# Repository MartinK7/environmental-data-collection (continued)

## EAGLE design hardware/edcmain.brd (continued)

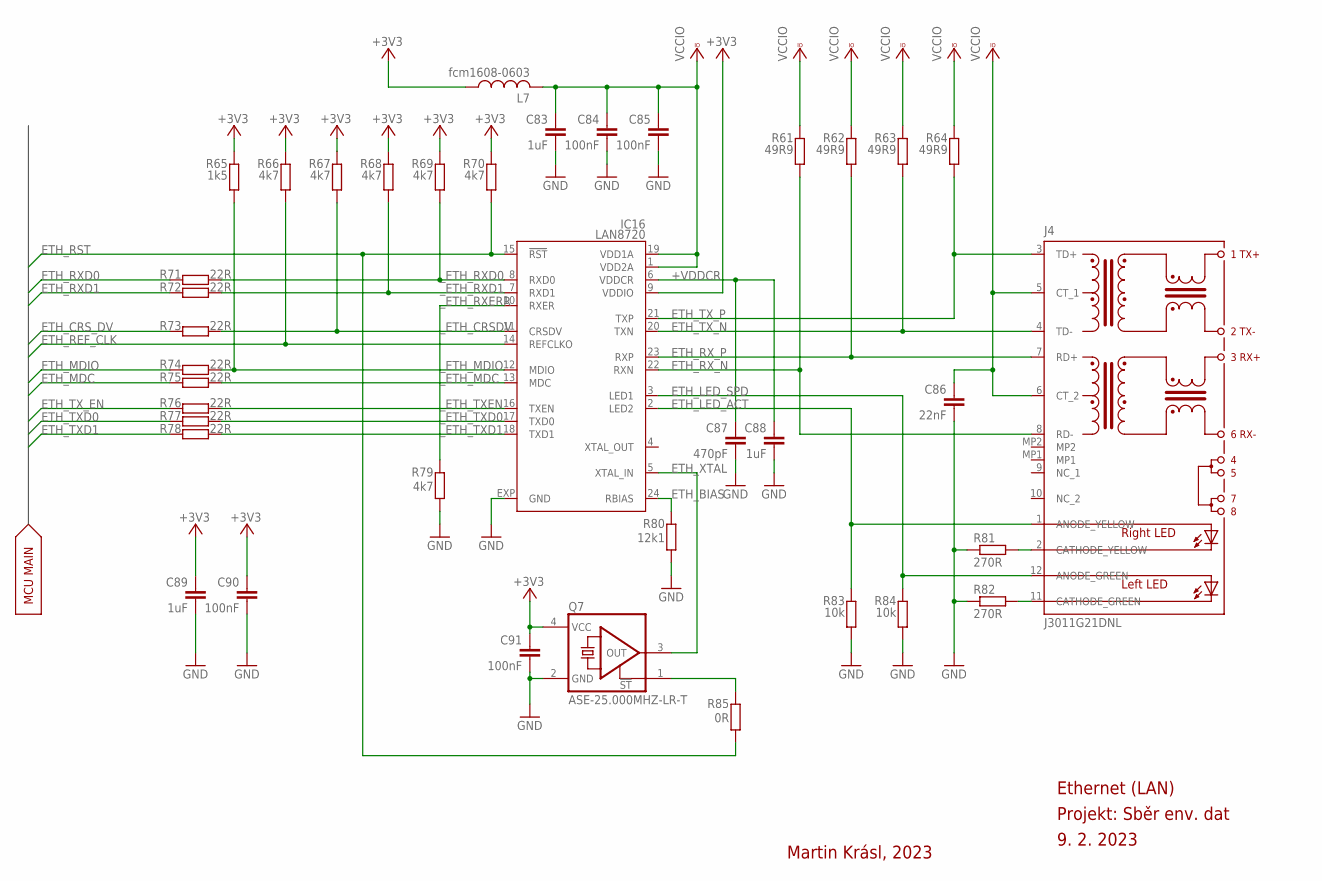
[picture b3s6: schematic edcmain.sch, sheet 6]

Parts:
C83, C88, C89: 1uF; C0402
C84, C85, C90, C91: 100nF; C0402
C86: 22nF; C0402
C87: 470pF; C0402
IC16: LAN8720; QFN24
J4: J3011G21DNL
L7: fcm1608-0603; L2012C
Q7: ASE-25.000MHZ-LR-T; CRYSTAL3.2X2.5
R61, R62, R63, R64: 49R9; R0402
R65: 1k5; R0402
R66, R67, R68, R69, R70, R79: 4k7; R0402
R71, R72, R73, R74, R75, R76, R77, R78: 22R; R0402
R80: 12k1; R0402
R81, R82: 270R; R0402
R83, R84: 10k; R0402
R85: 0R; R0402

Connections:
+3V3: C89.1, C90.1, C91.1, IC16.9 (VDDIO), L7.1, Q7.4 (VCC), R65.2, R66.2, R67.2, R68.2, R69.2, R70.2; also elsewhere on the board
+VDDCR: C87.1, C88.2, IC16.6 (VDDCR)
ETH_BIAS: IC16.24 (RBIAS), R80.1
ETH_CRS_DV: R73.1; also elsewhere on the board
ETH_LED_ACT: IC16.2 (LED2), J4.1 (ANODE_YELLOW), R83.2
ETH_LED_SPD: IC16.3 (LED1), J4.12 (ANODE_GREEN), R84.2
ETH_MDC: R75.1; also elsewhere on the board
ETH_MDIO: R74.1; also elsewhere on the board
ETH_REF_CLK: IC16.14 (REFCLKO), R66.1; also elsewhere on the board
ETH_RST: IC16.15 (!RST), R70.1, R85.2; also elsewhere on the board
ETH_RXD0: R71.1; also elsewhere on the board
ETH_RXD1: R72.1; also elsewhere on the board
ETH_RX_N: IC16.22 (RXN), J4.8 (RD-), R61.1
ETH_RX_P: IC16.23 (RXP), J4.7 (RD+), R62.1
ETH_TXD0: R77.1; also elsewhere on the board
ETH_TXD1: R78.1; also elsewhere on the board
ETH_TX_EN: R76.1; also elsewhere on the board
ETH_TX_N: IC16.20 (TXN), J4.4 (TD-), R63.1
ETH_TX_P: IC16.21 (TXP), J4.3 (TD+), R64.1
ETH_XTAL: IC16.5 (XTAL_IN), Q7.3 (OUT)
GND: C83.2, C84.2, C85.2, C86.2, C87.2, C88.1, C89.2, C90.2, C91.2, IC16.EXP (GND), Q7.2 (GND), R79.1, R80.2, R81.2, R82.2, R83.1, R84.1; also elsewhere on the board
unnamed: Q7.1 (!ST), R85.1
unnamed: J4.2 (CATHODE_YELLOW), R81.1
unnamed: J4.11 (CATHODE_GREEN), R82.1
VCCIO: C83.1, C84.1, C85.1, C86.1, IC16.1 (VDD2A), IC16.19 (VDD1A), J4.5 (CT_1), J4.6 (CT_2), L7.2, R61.2, R62.2, R63.2, R64.2
_ETH_CRSDV: IC16.11 (CRSDV), R67.1, R73.2
_ETH_MDC: IC16.13 (MDC), R75.2
_ETH_MDIO: IC16.12 (MDIO), R65.1, R74.2
_ETH_RXD0: IC16.8 (RXD0), R69.1, R71.2
_ETH_RXD1: IC16.7 (RXD1), R68.1, R72.2
_ETH_RXERR: IC16.10 (RXER), R79.2
_ETH_TXD0: IC16.17 (TXD0), R77.2
_ETH_TXD1: IC16.18 (TXD1), R78.2
_ETH_TXEN: IC16.16 (TXEN), R76.2

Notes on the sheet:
MCU MAIN
Ethernet (LAN)
Projekt: Sběr env. dat
9. 2. 2023
Martin Krásl, 2023

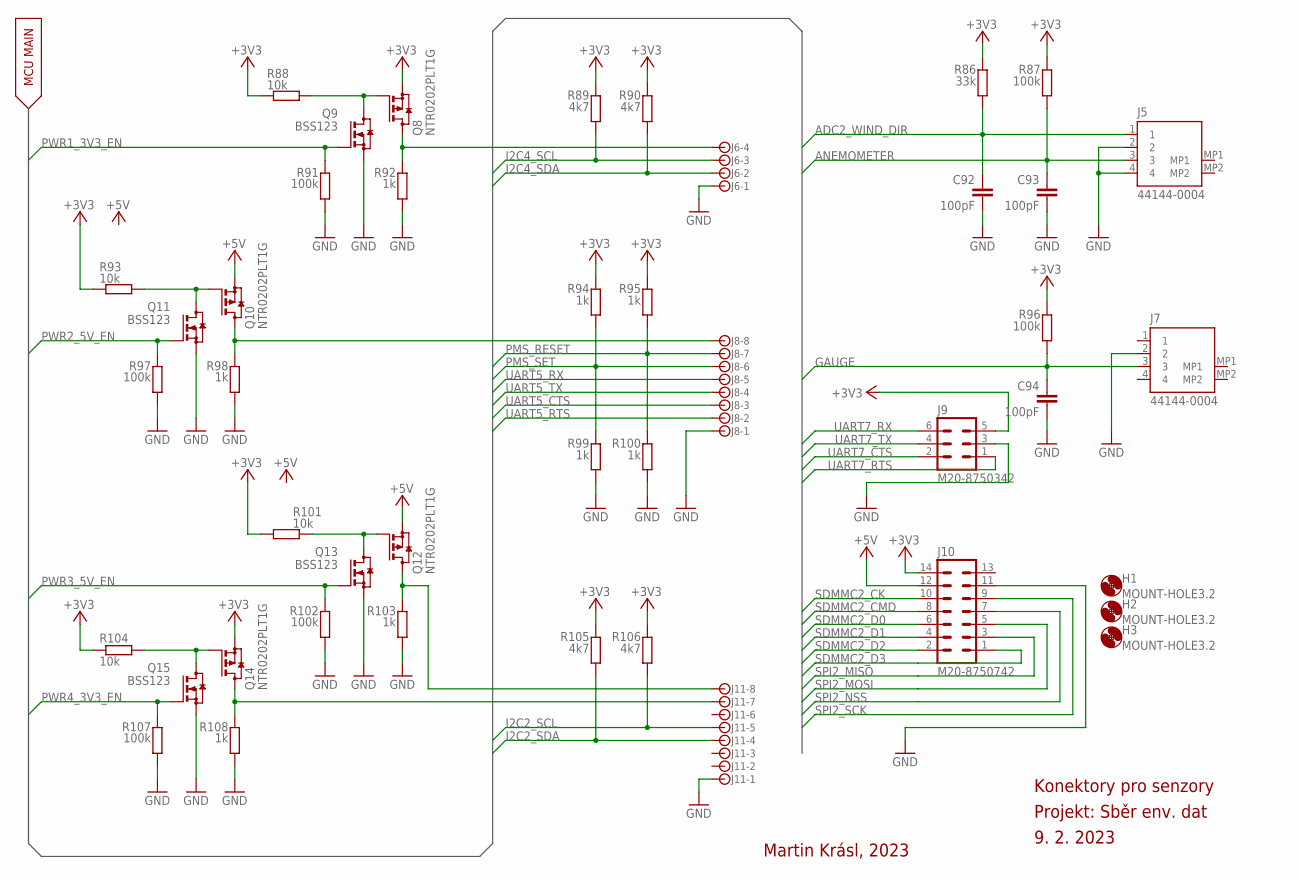
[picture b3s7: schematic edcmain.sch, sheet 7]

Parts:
C92, C93, C94: 100pF; C0402
H1, H2, H3: MOUNT-HOLE3.2; 3,2
J5, J7: 44144-0004; 441440004
J6: JST-XH-4; B4B-XH-A
J8, J11: JST-XH-8; B8B-XH-A
J9: M20-8750342; M208750342
J10: M20-8750742; M208750742
Q8, Q10, Q12, Q14: NTR0202PLT1G; SOT23
Q9, Q11, Q13, Q15: BSS123; SOT23
R86: 33k; R0402
R87, R91, R96, R97, R102, R107: 100k; R0402
R88, R93, R101, R104: 10k; R0402
R89, R90, R105, R106: 4k7; R0402
R92, R94, R95, R98, R99, R100, R103, R108: 1k; R0402

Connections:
+3V3: J9.5, J10.14, Q8.2 (S), Q14.2 (S), R86.2, R87.2, R88.1, R89.2, R90.2, R93.1, R94.2, R95.2, R96.2, R101.1, R104.1, R105.2, R106.2; also elsewhere on the board
+5V: J10.12, Q10.2 (S), Q12.2 (S); also elsewhere on the board
ADC2_WIND_DIR: C92.1, J5.1, R86.1; also elsewhere on the board
ANEMOMETER: C93.1, J5.3, R87.1; also elsewhere on the board
GAUGE: C94.1, J7.3, R96.1; also elsewhere on the board
GND: C92.2, C93.2, C94.2, J5.2, J5.4, J6.1, J7.2, J8.1, J9.3, J10.11, J11.1, Q9.2 (S), Q11.2 (S), Q13.2 (S), Q15.2 (S), R91.1, R92.1, R97.1, R98.1, R99.1, R100.1, R102.1, R103.1, R107.1, R108.1; also elsewhere on the board
I2C2_SCL: J11.5, R106.1; also elsewhere on the board
I2C2_SDA: J11.4, R105.1; also elsewhere on the board
I2C4_SCL: J6.3, R89.1; also elsewhere on the board
I2C4_SDA: J6.2, R90.1; also elsewhere on the board
unnamed: J11.7, Q14.3 (D), R108.2
unnamed: J11.8, Q12.3 (D), R103.2
unnamed: Q12.1 (G), Q13.3 (D), R101.2
unnamed: Q10.1 (G), Q11.3 (D), R93.2
unnamed: J8.8, Q10.3 (D), R98.2
unnamed: Q8.1 (G), Q9.3 (D), R88.2
unnamed: J6.4, Q8.3 (D), R92.2
unnamed: Q14.1 (G), Q15.3 (D), R104.2
PMS_RESET: J8.7, R95.1, R100.2; also elsewhere on the board
PMS_SET: J8.6, R94.1, R99.2; also elsewhere on the board
PWR1_3V3_EN: Q9.1 (G), R91.2; also elsewhere on the board
PWR2_5V_EN: Q11.1 (G), R97.2; also elsewhere on the board
PWR3_5V_EN: Q13.1 (G), R102.2; also elsewhere on the board
PWR4_3V3_EN: Q15.1 (G), R107.2; also elsewhere on the board
SDMMC2_CK: J10.10; also elsewhere on the board
SDMMC2_CMD: J10.8; also elsewhere on the board
SDMMC2_D0: J10.6; also elsewhere on the board
SDMMC2_D1: J10.4; also elsewhere on the board
SDMMC2_D2: J10.2; also elsewhere on the board
SDMMC2_D3: J10.1; also elsewhere on the board
SPI2_MISO: J10.3; also elsewhere on the board
SPI2_MOSI: J10.5; also elsewhere on the board
SPI2_NSS: J10.7; also elsewhere on the board
SPI2_SCK: J10.9; also elsewhere on the board
UART5_CTS: J8.3; also elsewhere on the board
UART5_RTS: J8.2; also elsewhere on the board
UART5_RX: J8.5; also elsewhere on the board
UART5_TX: J8.4; also elsewhere on the board
UART7_CTS: J9.2; also elsewhere on the board
UART7_RTS: J9.1; also elsewhere on the board
UART7_RX: J9.6; also elsewhere on the board
UART7_TX: J9.4; also elsewhere on the board

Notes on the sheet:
MCU MAIN
Konektory pro senzory
Projekt: Sběr env. dat
9. 2. 2023
Martin Krásl, 2023

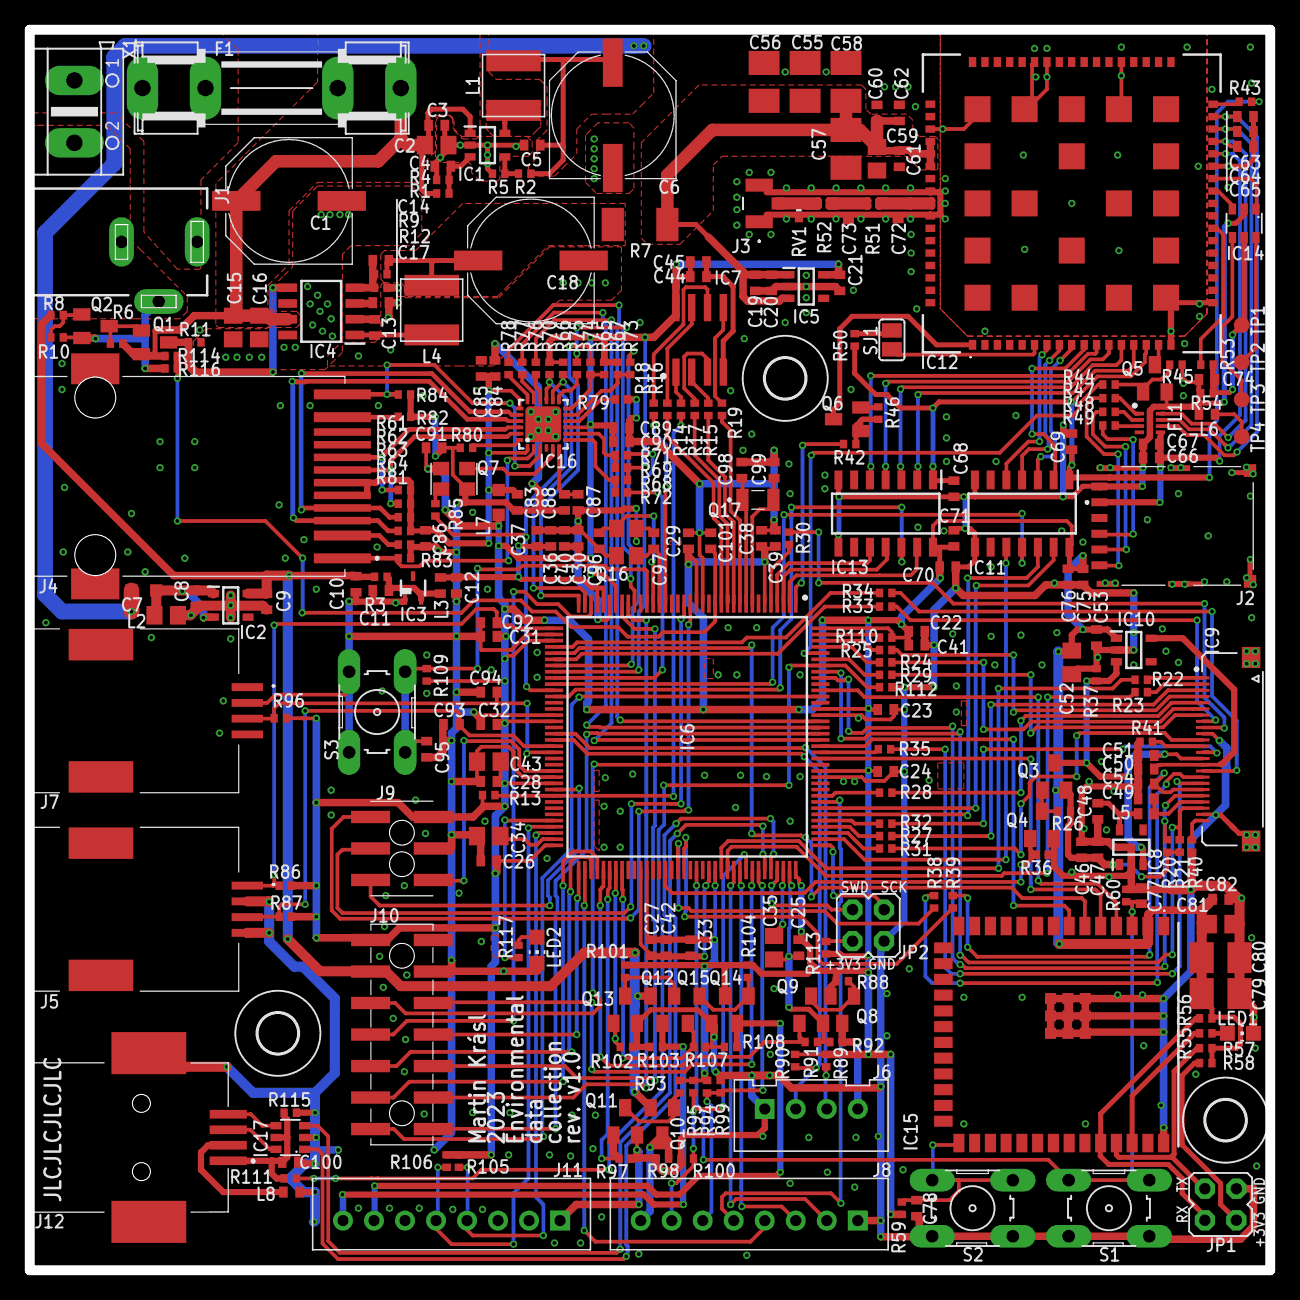
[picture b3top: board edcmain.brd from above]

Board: 2 copper layers, 100.0 x 100.0 mm, 292 parts (1 on the bottom side), 222 nets.

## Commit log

2023-09-24 squashed: initial files
2023-10-06 Create LICENSE
